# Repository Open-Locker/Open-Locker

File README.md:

# Open-Locker

<p align="center">
  
</p>

Open-Locker is an open source software and hardware platform for public lockers
used to store and share resources. The project includes the cloud services,
mobile experience, on-site controller, public website, and hardware blueprints
needed to run a deployment.

The project began with lockers operated by the county of Hameln-Pyrmont for
lending equipment such as laptops and VR headsets. It is sponsored by
[Smart City Hameln-Pyrmont](https://mitwirkportal.de/informieren) and developed
by a community learning together while building useful public infrastructure.

## How the system works

The React Native mobile app uses the Laravel API to discover accessible
compartments, update their content notes, and request that a compartment open.
The backend authorizes and records those operations through event-sourced domain
workflows. It sends hardware commands over MQTT to a Raspberry Pi running
`locker-client`; only that client communicates with the relay boards over
serialized Modbus RTU. Laravel Reverb carries compartment updates; the current
mobile app applies live door-state and content-note changes.

See [the architecture overview](docs/Architecture.md) for system boundaries,
[the app communication guide](docs/app_communication.md) for REST and realtime
behavior, and [the AsyncAPI contract](docs/asyncapi/mqtt.yaml) for MQTT topics
and payloads.

## Repository structure

```text
Open-Locker/
├── locker-backend/  # Laravel 12 API, Filament 5 admin, MQTT, and Reverb
├── locker-client/   # Raspberry Pi MQTT-to-Modbus RTU bridge and simulator
├── mobile-app/      # React Native and Expo client
├── website/         # Astro public website and published documentation
├── hardware/        # KiCad designs and build references
├── docs/            # Architecture, contracts, ADRs, and operating guides
└── Justfile         # Repository task runner
```

The backend runs on PostgreSQL and exposes a live Scramble-generated OpenAPI
document at `/docs/api.json`. The mobile app generates its RTK Query client from
that live contract.

## Getting started

Repository commands use Just 1.56+ and Node 22+ for MQTT setup and tracing.
Install the pinned script dependencies with `just script-deps` (pnpm 11.25.0).
The TypeScript workflows use tsx, Execa and dotenv in a separate `scripts/` package.
Docker and Git are needed by their respective commands;
the simulator also needs pnpm and the locker-client dependencies.

```text
just --list
just start
just status
just trace-up
```

`just --dry-run trace-up` previews the pnpm invocation. To preview the workflow's
internal actions without writing files or starting services, use
`pnpm --dir scripts trace up --dry-run`. The same script runs on Windows, Linux
and macOS. Run `pnpm --dir scripts check` for type checking and
`pnpm --dir scripts test` for tests. See [the script guide](scripts/README.md)
and [ADR-0060](docs/adr/0060-just-node-repository-workflows.md).

Use [the installation guide](docs/Installation.md) for backend and Raspberry Pi
setup. Component-specific details live in:

- [Backend documentation](locker-backend/README.md)
- [Locker client documentation](locker-client/README.md)
- [Website documentation](website/README.md)
- [Hardware-free simulator guide](docs/simulator.md)

## Community

Join our weekly meeting every Tuesday at **19:30 CET / 18:30 UTC** on
[Discord](https://discord.gg/rZ74RYKN3H), or participate through GitHub issues,
pull requests, and feedback. New contributors are welcome to listen in, ask
questions, or choose a component that interests them.

The repository is also mirrored on
[openCode](https://gitlab.opencode.de/OC000075481431/open-locker) for Public
Money, Public Code publication.

We also welcome organizations interested in sponsoring or adopting open digital
infrastructure for community resource sharing. Contact the project through
Discord or open a GitHub issue.

Please check out the [Code of Conduct](CODE_OF_CONDUCT.md) to see how to properly interact with our community.

If you want to contact us, you can reach out via
[Discord](https://discord.gg/rZ74RYKN3H) or email us at
[moin@merona.de](mailto:moin@merona.de).

To report a security vulnerability, see [SECURITY.md](SECURITY.md).

## License

Open-Locker is available under the [AGPL v3](LICENSE.md).

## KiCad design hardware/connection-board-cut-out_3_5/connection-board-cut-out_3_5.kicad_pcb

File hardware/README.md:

# Open-Locker Hardware Boards

This directory contains Open-Locker PCB and mechanical design files.

The current boards are connection/distribution boards. They simplify cabinet
wiring, but they do not replace the controller or the supported Modbus
relay/input board.

For the recommended hardware direction, see:

- [`docs/Hardware-Integration-Concept.md`](../docs/Hardware-Integration-Concept.md)
- [`docs/adr/0018-integrated-carrier-pcb-first.md`](../docs/adr/0018-integrated-carrier-pcb-first.md)
- [`docs/Bill-of-Materials.md`](../docs/Bill-of-Materials.md)

## PCB Projects

| Path | Purpose | Notes |
| --- | --- | --- |
| [`connection-board-cut-out_3_5`](connection-board-cut-out_3_5) | Recommended connection board for repeatable cabinet wiring. | Uses 3.5 mm screw terminals, which are easier to wire and service in the field. |
| [`connection-board-cut-out_2_54`](connection-board-cut-out_2_54) | Alternate connection board layout. | Uses smaller connector footprints. Pick only if the cabinet harness and connector pitch match. |
| [`mtu-connection-board`](mtu-connection-board) | MTU-specific connection board. | Cabinet/form-factor specific variant. |
| [`mtu-connection-board-large`](mtu-connection-board-large) | Larger MTU-specific connection board. | Cabinet/form-factor specific variant. |
| [`models`](models) | OpenSCAD mechanical helper parts. | Includes lock spacers and PCB mounting adapters. Export STL files from these sources when needed. |

## What the Connection Board Does

The connection board is intended to make the inside of a locker cabinet easier
to assemble and debug.

Logical responsibilities:

- route lock wiring for up to eight compartments
- route feedback switch wiring for up to eight compartments
- place one flyback diode per lock channel
- provide labeled connection points between the cabinet harness and the
  supported relay/input board
- provide power and RS485 connection points for the cabinet wiring path

The board should be treated as a wiring aid. The active relay timing and digital
input behavior still come from the supported relay/input hardware and the
locker-client software.

## Current Supported Relay/Input Board

The validated Modbus relay/input board is:

- Waveshare `Modbus RTU Relay (D)`

Open-Locker currently depends on verified Waveshare hardware flash behavior for
safe lock release pulses. See:

- [`docs/adr/0004-waveshare-hardware-flash-and-supported-boards.md`](../docs/adr/0004-waveshare-hardware-flash-and-supported-boards.md)
- [`locker-client/docs/WAVESHARE_INTEGRATION.md`](../locker-client/docs/WAVESHARE_INTEGRATION.md)

## Before Manufacturing or Wiring

Before ordering PCBs or wiring a cabinet:

1. Open the KiCad project for the selected board.
2. Verify the schematic against the intended lock, relay, power, and RS485
   wiring.
3. Verify connector pitch and orientation against the physical connectors.
4. Confirm trace widths and connector ratings for the lock current.
5. Label the cabinet harness to match compartment numbers, relay addresses, and
   digital input addresses.
6. Bench-test with current-limited 12 V power before connecting all locks.

Exact connector pinouts should be documented in a future wiring guide after the
selected board revision and cabinet harness are validated.

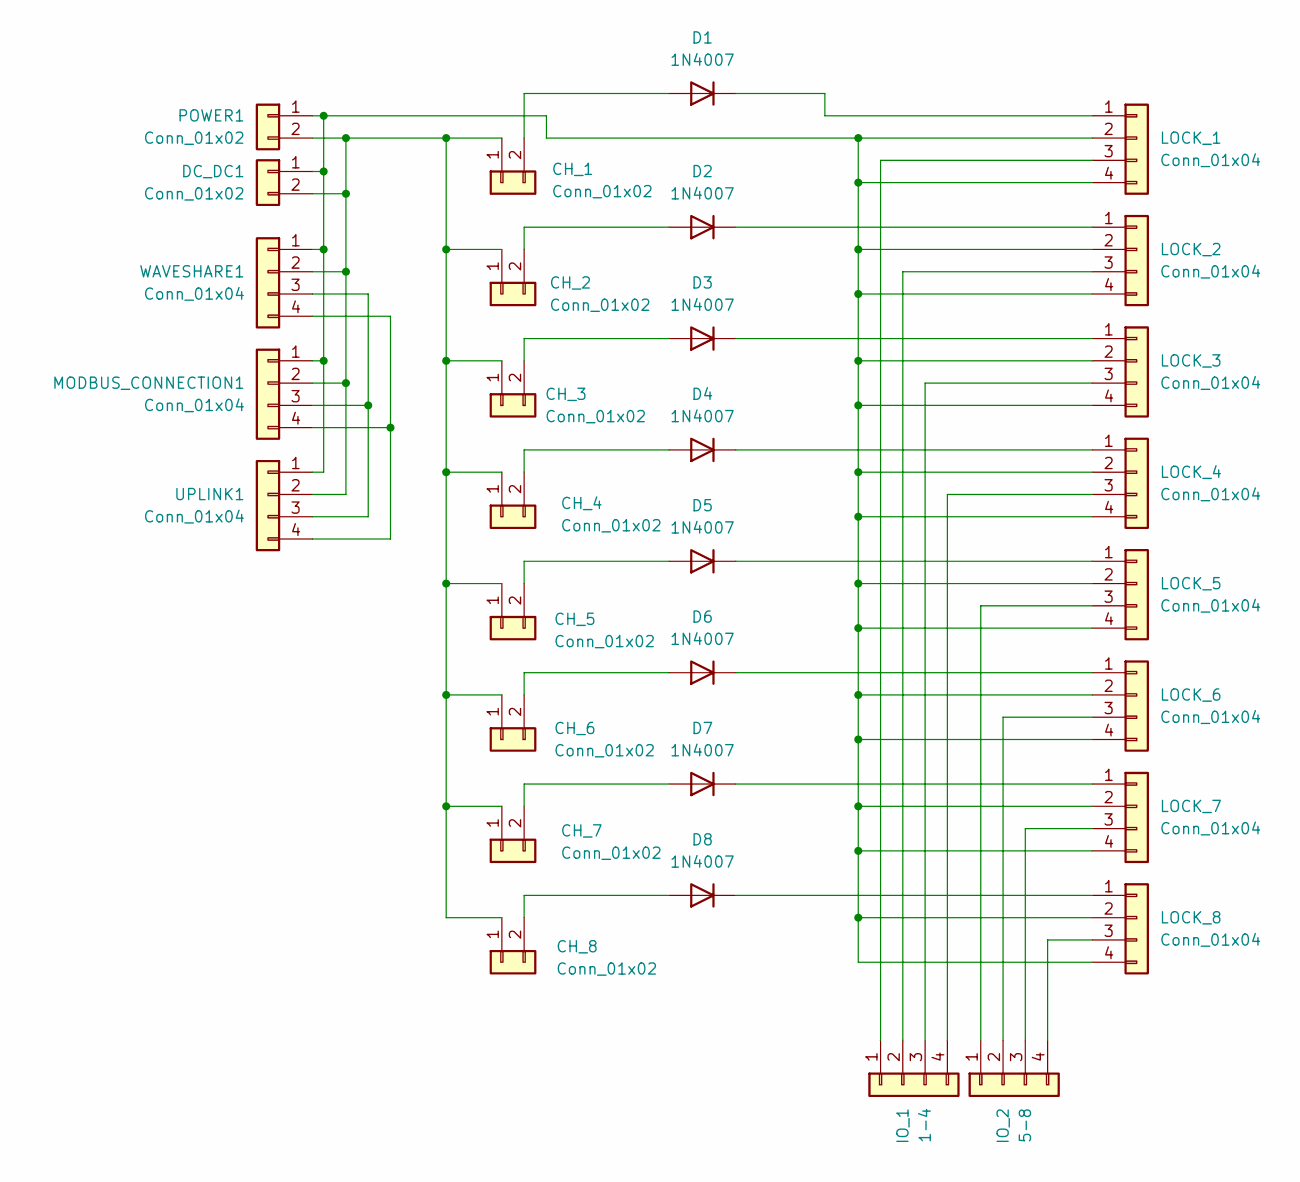
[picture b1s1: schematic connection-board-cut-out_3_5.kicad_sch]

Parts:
CH_1, CH_2, CH_3, CH_4, CH_5, CH_6, CH_7, CH_8: Conn_01x02; PhoenixContact_MCV_1,5_2-G-3.5_1x02_P3.50mm_Vertical
D1, D2, D3, D4, D5, D6, D7, D8: 1N4007; D_DO-41_SOD81_P10.16mm_Horizontal
DC_DC1: Conn_01x02; PhoenixContact_MCV_1,5_2-G-3.5_1x02_P3.50mm_Vertical
IO_1: 1-4; PhoenixContact_MCV_1,5_4-G-3.5_1x04_P3.50mm_Vertical
IO_2: 5-8; PhoenixContact_MCV_1,5_4-G-3.5_1x04_P3.50mm_Vertical
LOCK_1, LOCK_2, LOCK_3, LOCK_4, LOCK_5, LOCK_6, LOCK_7, LOCK_8: Conn_01x04; PhoenixContact_MCV_1,5_4-G-3.5_1x04_P3.50mm_Vertical
MODBUS_CONNECTION1: Conn_01x04; PhoenixContact_MCV_1,5_4-G-3.5_1x04_P3.50mm_Vertical
POWER1: Conn_01x02; PhoenixContact_MCV_1,5_2-G-3.5_1x02_P3.50mm_Vertical
UPLINK1: Conn_01x04; PhoenixContact_MCV_1,5_4-G-3.5_1x04_P3.50mm_Vertical
WAVESHARE1: Conn_01x04; PhoenixContact_MCV_1,5_4-G-3.5_1x04_P3.50mm_Vertical

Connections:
unnamed: CH_1.1, CH_2.1, CH_3.1, CH_4.1, CH_5.1, CH_6.1, CH_7.1, CH_8.1, DC_DC1.2, MODBUS_CONNECTION1.2, POWER1.2, UPLINK1.2, WAVESHARE1.2
unnamed: CH_1.2, D1.2 (A)
unnamed: CH_2.2, D2.2 (A)
unnamed: CH_3.2, D3.2 (A)
unnamed: CH_4.2, D4.2 (A)
unnamed: CH_5.2, D5.2 (A)
unnamed: CH_6.2, D6.2 (A)
unnamed: CH_7.2, D7.2 (A)
unnamed: CH_8.2, D8.2 (A)
unnamed: D1.1 (K), LOCK_1.1
unnamed: D2.1 (K), LOCK_2.1
unnamed: D3.1 (K), LOCK_3.1
unnamed: D4.1 (K), LOCK_4.1
unnamed: D5.1 (K), LOCK_5.1
unnamed: D6.1 (K), LOCK_6.1
unnamed: D7.1 (K), LOCK_7.1
unnamed: D8.1 (K), LOCK_8.1
unnamed: DC_DC1.1, LOCK_1.2, LOCK_1.4, LOCK_2.2, LOCK_2.4, LOCK_3.2, LOCK_3.4, LOCK_4.2, LOCK_4.4, LOCK_5.2, LOCK_5.4, LOCK_6.2, LOCK_6.4, LOCK_7.2, LOCK_7.4, LOCK_8.2, LOCK_8.4, MODBUS_CONNECTION1.1, POWER1.1, UPLINK1.1, WAVESHARE1.1
unnamed: IO_1.1, LOCK_1.3
unnamed: IO_1.2, LOCK_2.3
unnamed: IO_1.3, LOCK_3.3
unnamed: IO_1.4, LOCK_4.3
unnamed: IO_2.1, LOCK_5.3
unnamed: IO_2.2, LOCK_6.3
unnamed: IO_2.3, LOCK_7.3
unnamed: IO_2.4, LOCK_8.3
unnamed: MODBUS_CONNECTION1.3, UPLINK1.3, WAVESHARE1.3
unnamed: MODBUS_CONNECTION1.4, UPLINK1.4, WAVESHARE1.4

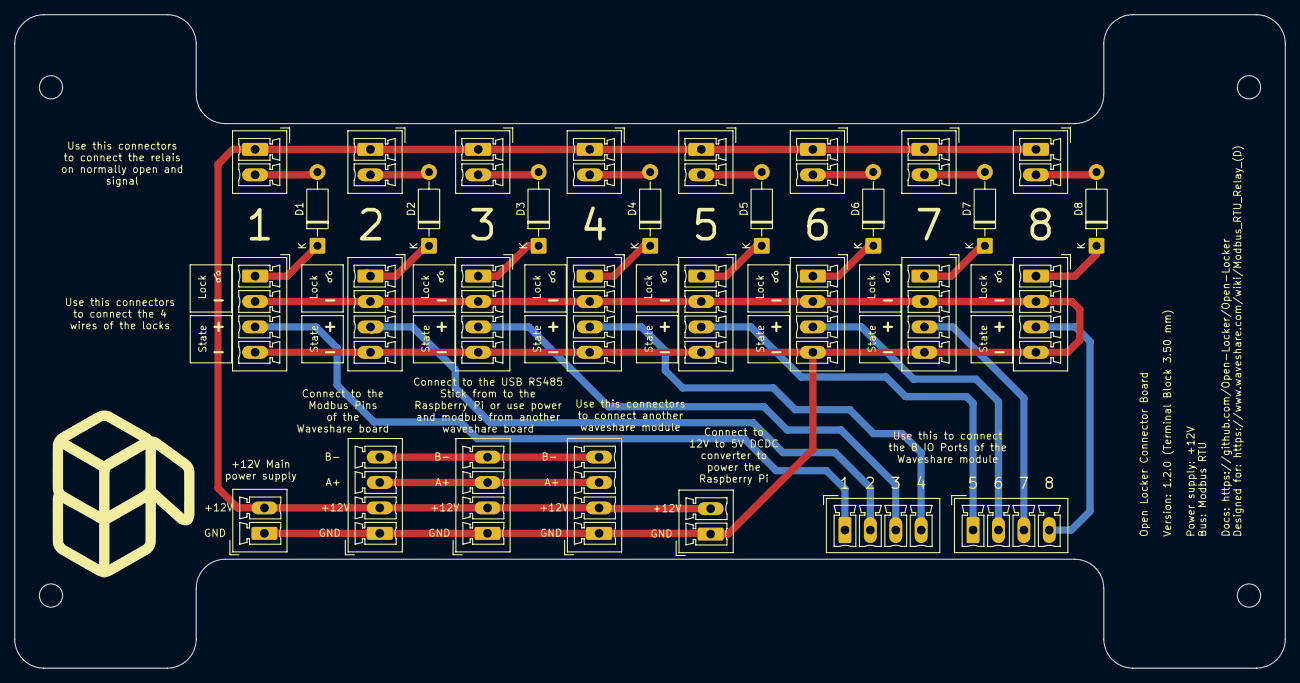
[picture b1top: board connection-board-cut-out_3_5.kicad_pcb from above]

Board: 2 copper layers, 175.0 x 90.0 mm, 31 parts (0 on the bottom side), 28 nets.

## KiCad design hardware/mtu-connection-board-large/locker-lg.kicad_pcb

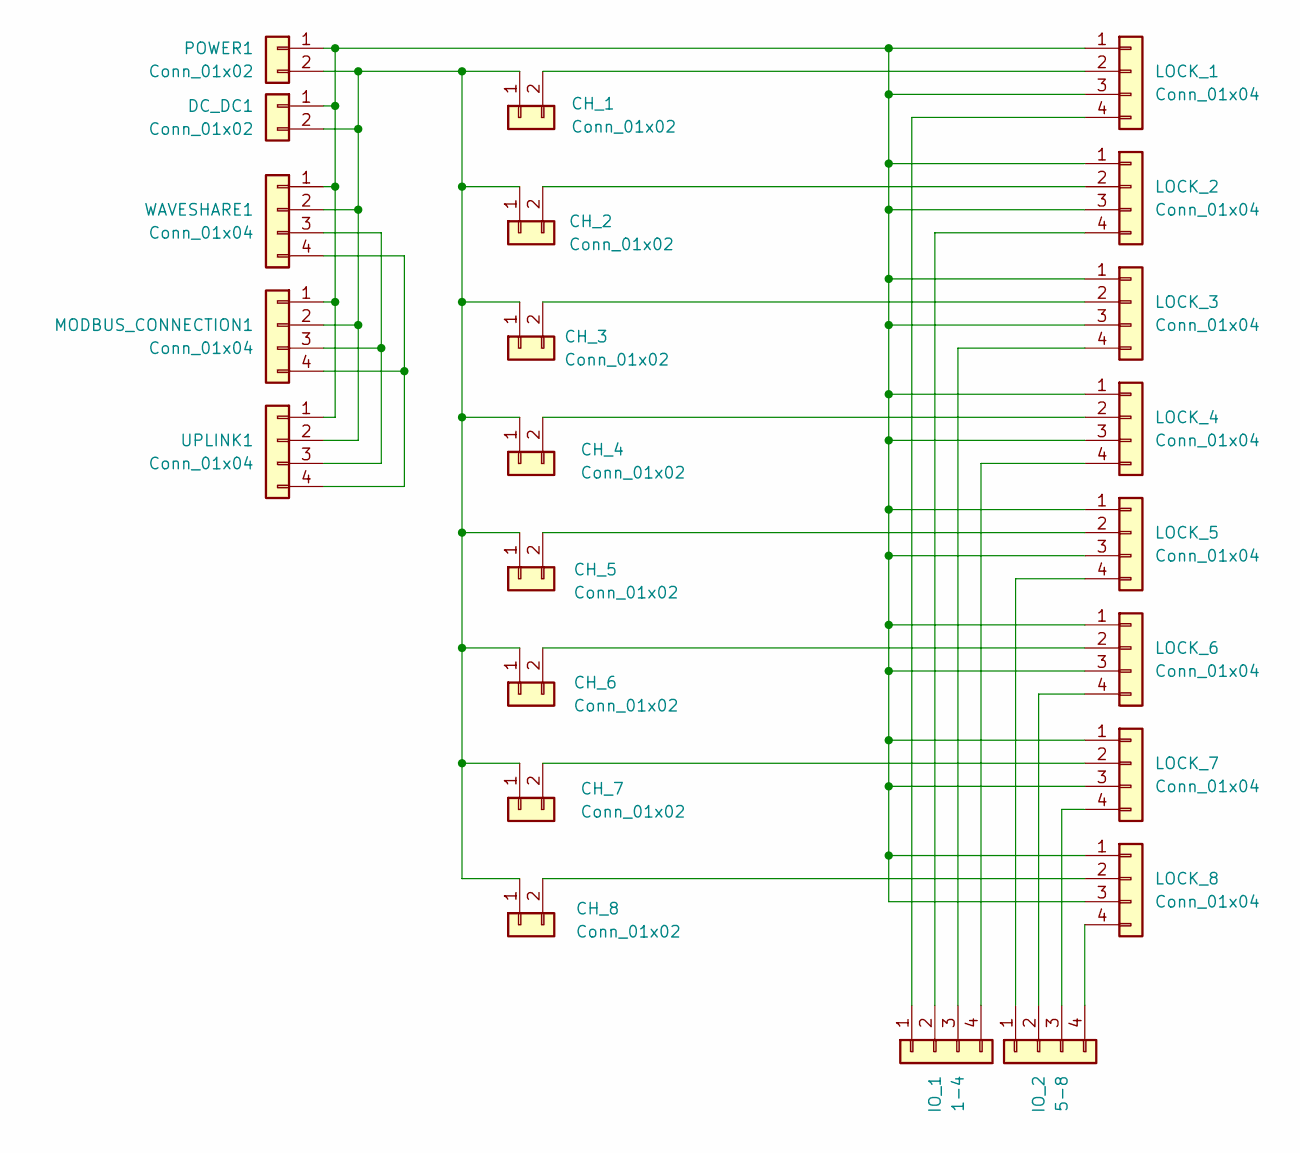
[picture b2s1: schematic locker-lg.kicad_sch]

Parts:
CH_1, CH_2, CH_3, CH_4, CH_5, CH_6, CH_7, CH_8: Conn_01x02; JST_XH_B2B-XH-A_1x02_P2.50mm_Vertical
DC_DC1: Conn_01x02; JST_XH_B2B-XH-A_1x02_P2.50mm_Vertical
IO_1: 1-4; JST_XH_B4B-XH-A_1x04_P2.50mm_Vertical
IO_2: 5-8; JST_XH_B4B-XH-A_1x04_P2.50mm_Vertical
LOCK_1, LOCK_2, LOCK_3, LOCK_4, LOCK_5, LOCK_6, LOCK_7, LOCK_8: Conn_01x04; JST_XH_B4B-XH-A_1x04_P2.50mm_Vertical
MODBUS_CONNECTION1: Conn_01x04; JST_XH_B4B-XH-A_1x04_P2.50mm_Vertical
POWER1: Conn_01x02; JST_XH_B2B-XH-A_1x02_P2.50mm_Vertical
UPLINK1: Conn_01x04; JST_XH_B4B-XH-A_1x04_P2.50mm_Vertical
WAVESHARE1: Conn_01x04; JST_XH_B4B-XH-A_1x04_P2.50mm_Vertical

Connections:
unnamed: CH_1.1, CH_2.1, CH_3.1, CH_4.1, CH_5.1, CH_6.1, CH_7.1, CH_8.1, DC_DC1.2, MODBUS_CONNECTION1.2, POWER1.2, UPLINK1.2, WAVESHARE1.2
unnamed: CH_1.2, LOCK_1.2
unnamed: CH_2.2, LOCK_2.2
unnamed: CH_3.2, LOCK_3.2
unnamed: CH_4.2, LOCK_4.2
unnamed: CH_5.2, LOCK_5.2
unnamed: CH_6.2, LOCK_6.2
unnamed: CH_7.2, LOCK_7.2
unnamed: CH_8.2, LOCK_8.2
unnamed: DC_DC1.1, LOCK_1.1, LOCK_1.3, LOCK_2.1, LOCK_2.3, LOCK_3.1, LOCK_3.3, LOCK_4.1, LOCK_4.3, LOCK_5.1, LOCK_5.3, LOCK_6.1, LOCK_6.3, LOCK_7.1, LOCK_7.3, LOCK_8.1, LOCK_8.3, MODBUS_CONNECTION1.1, POWER1.1, UPLINK1.1, WAVESHARE1.1
unnamed: IO_1.1, LOCK_1.4
unnamed: IO_1.2, LOCK_2.4
unnamed: IO_1.3, LOCK_3.4
unnamed: IO_1.4, LOCK_4.4
unnamed: IO_2.1, LOCK_5.4
unnamed: IO_2.2, LOCK_6.4
unnamed: IO_2.3, LOCK_7.4
unnamed: IO_2.4, LOCK_8.4
unnamed: MODBUS_CONNECTION1.3, UPLINK1.3, WAVESHARE1.3
unnamed: MODBUS_CONNECTION1.4, UPLINK1.4, WAVESHARE1.4

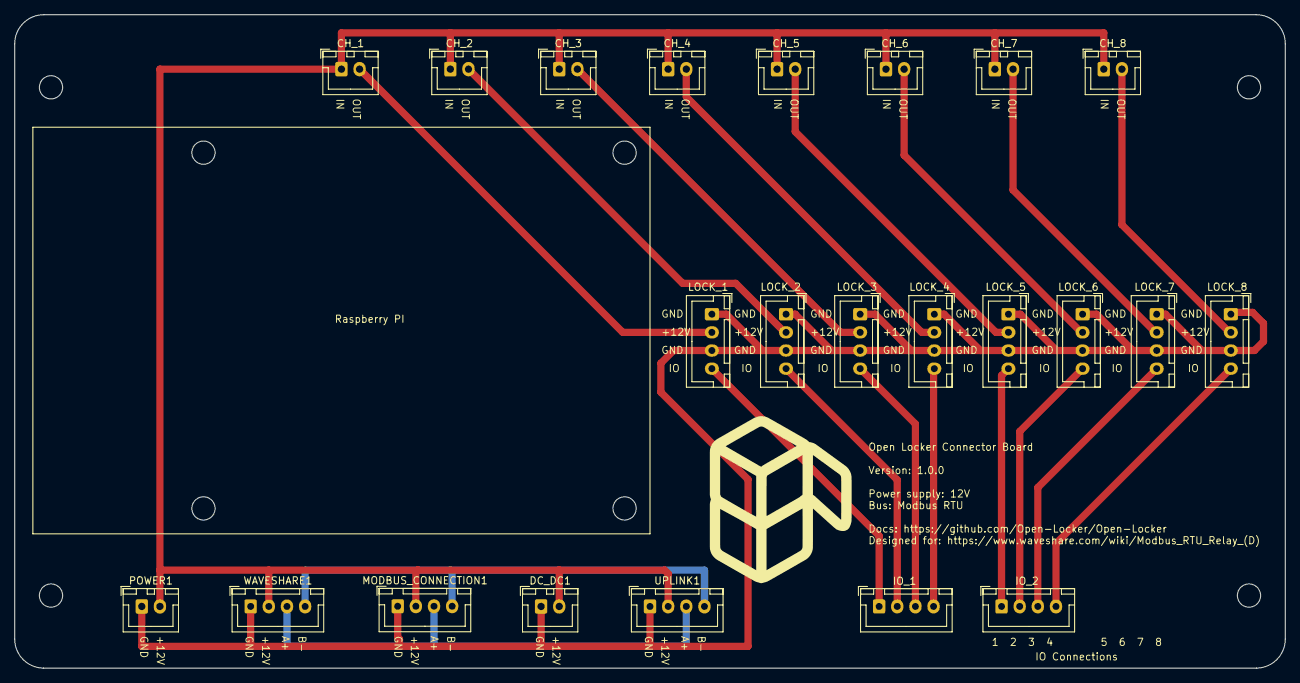
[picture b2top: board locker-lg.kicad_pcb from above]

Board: 2 copper layers, 175.0 x 90.0 mm, 23 parts (0 on the bottom side), 20 nets.
